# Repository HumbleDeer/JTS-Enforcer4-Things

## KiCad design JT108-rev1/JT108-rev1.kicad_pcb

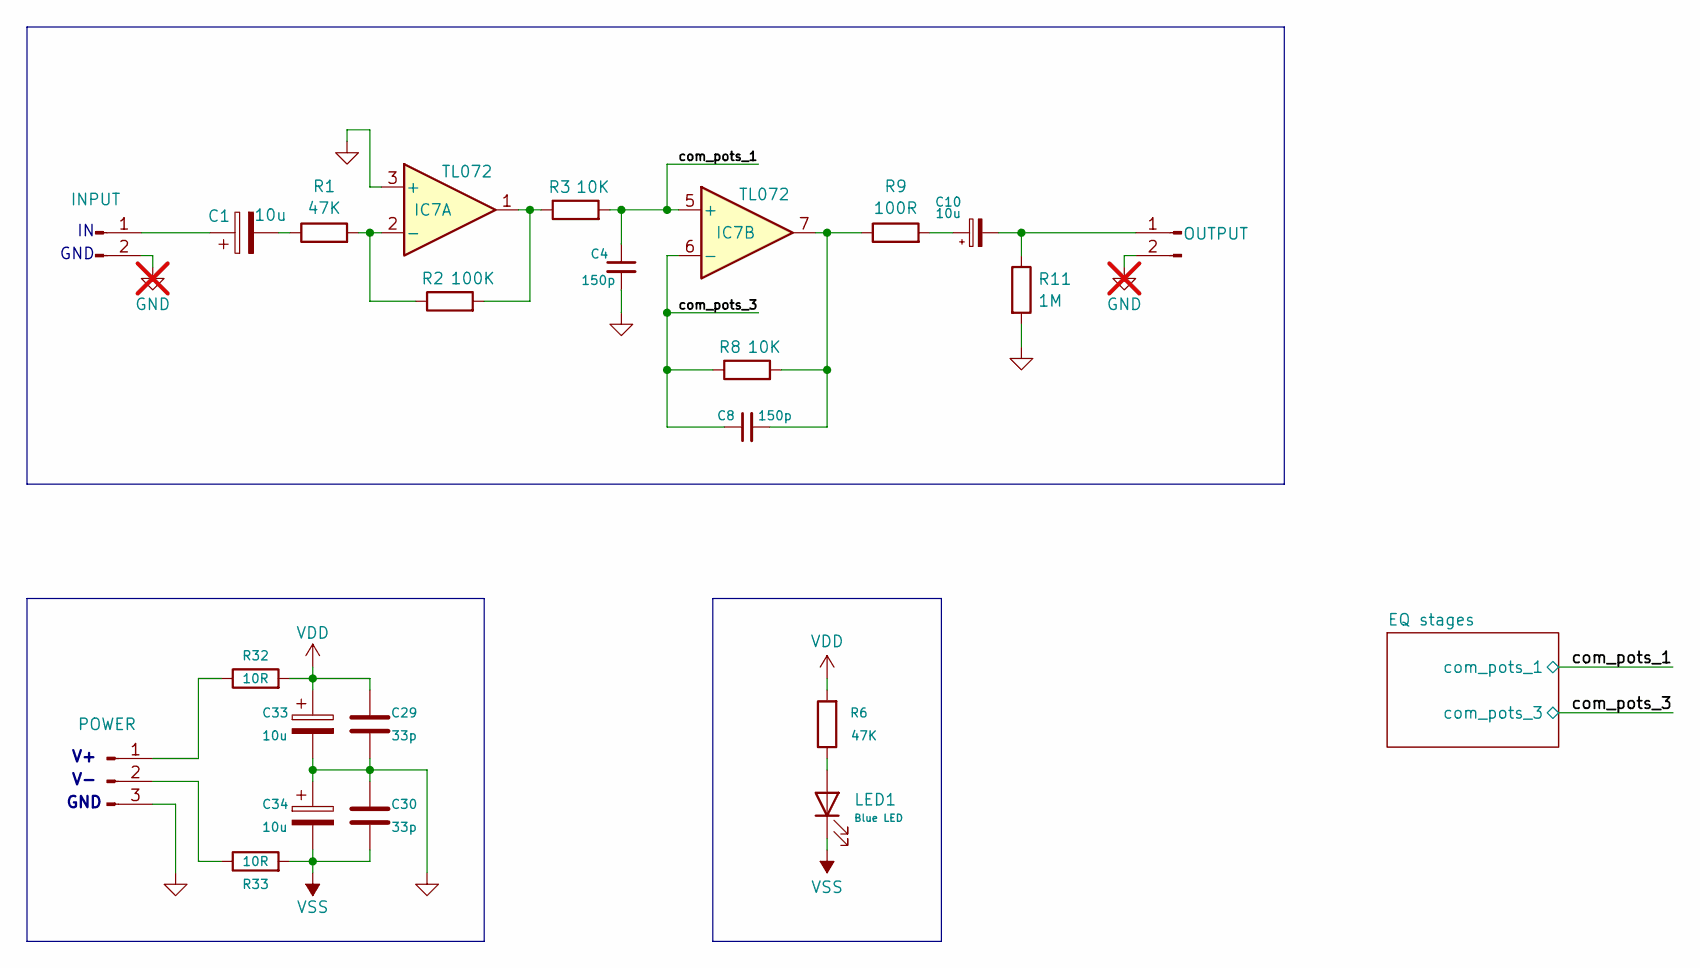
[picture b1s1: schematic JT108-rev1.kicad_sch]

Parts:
C1: 10u; CP_Radial_D5.0mm_P2.00mm
C4, C8: 150p; C_Disc_D5.0mm_W2.5mm_P2.50mm
C10, C33, C34: 10u; CP_Radial_D6.3mm_P2.50mm
C29, C30: 33p; C_Disc_D5.0mm_W2.5mm_P2.50mm
IC7: TL072; DIP-8_W7.62mm
J1: INPUT; PinHeader_1x01_P2.54mm_Vertical
J2: OUTPUT; PinHeader_1x01_P2.54mm_Vertical
J3: POWER; JST_VH_B3P-VH_1x03_P3.96mm_Vertical
LED1: Blue LED; LED_D5.0mm
R1: 47K; R_Axial_DIN0207_L6.3mm_D2.5mm_P10.16mm_Horizontal
R2: 100K; R_Axial_DIN0207_L6.3mm_D2.5mm_P10.16mm_Horizontal
R3, R8: 10K; R_Axial_DIN0207_L6.3mm_D2.5mm_P10.16mm_Horizontal
R6: 47K; R_Axial_DIN0207_L6.3mm_D2.5mm_P2.54mm_Vertical
R9: 100R; R_Axial_DIN0207_L6.3mm_D2.5mm_P10.16mm_Horizontal
R11: 1M; R_Axial_DIN0207_L6.3mm_D2.5mm_P10.16mm_Horizontal
R32, R33: 10R; R_Axial_DIN0207_L6.3mm_D2.5mm_P10.16mm_Horizontal

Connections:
/com_pots_1: C4.1, IC7.5 (+), R3.2; also elsewhere on the board
/com_pots_3: C8.1, IC7.6 (-), R8.1; also elsewhere on the board
GND: C4.2, C29.1, C30.1, C33.2, C34.1, IC7.3 (+), J1.2, J2.2, J3.3, R11.2; also elsewhere on the board
unnamed: C1.2, R1.1
unnamed: C8.2, IC7.7, R8.2, R9.1
unnamed: C10.1, R9.2
unnamed: IC7.1, R2.2, R3.1
unnamed: IC7.2 (-), R1.2, R2.1
unnamed: C1.1, J1.1 (Pin_1_1)
unnamed: C10.2, J2.1 (Pin_1_1), R11.1
unnamed: J3.1, R32.1
unnamed: J3.2, R33.1
unnamed: LED1.2 (A), R6.1
VDD: C29.2, C33.1, R6.2, R32.2; also elsewhere on the board
VSS: C30.2, C34.2, LED1.1 (K), R33.2; also elsewhere on the board

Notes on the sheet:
GND

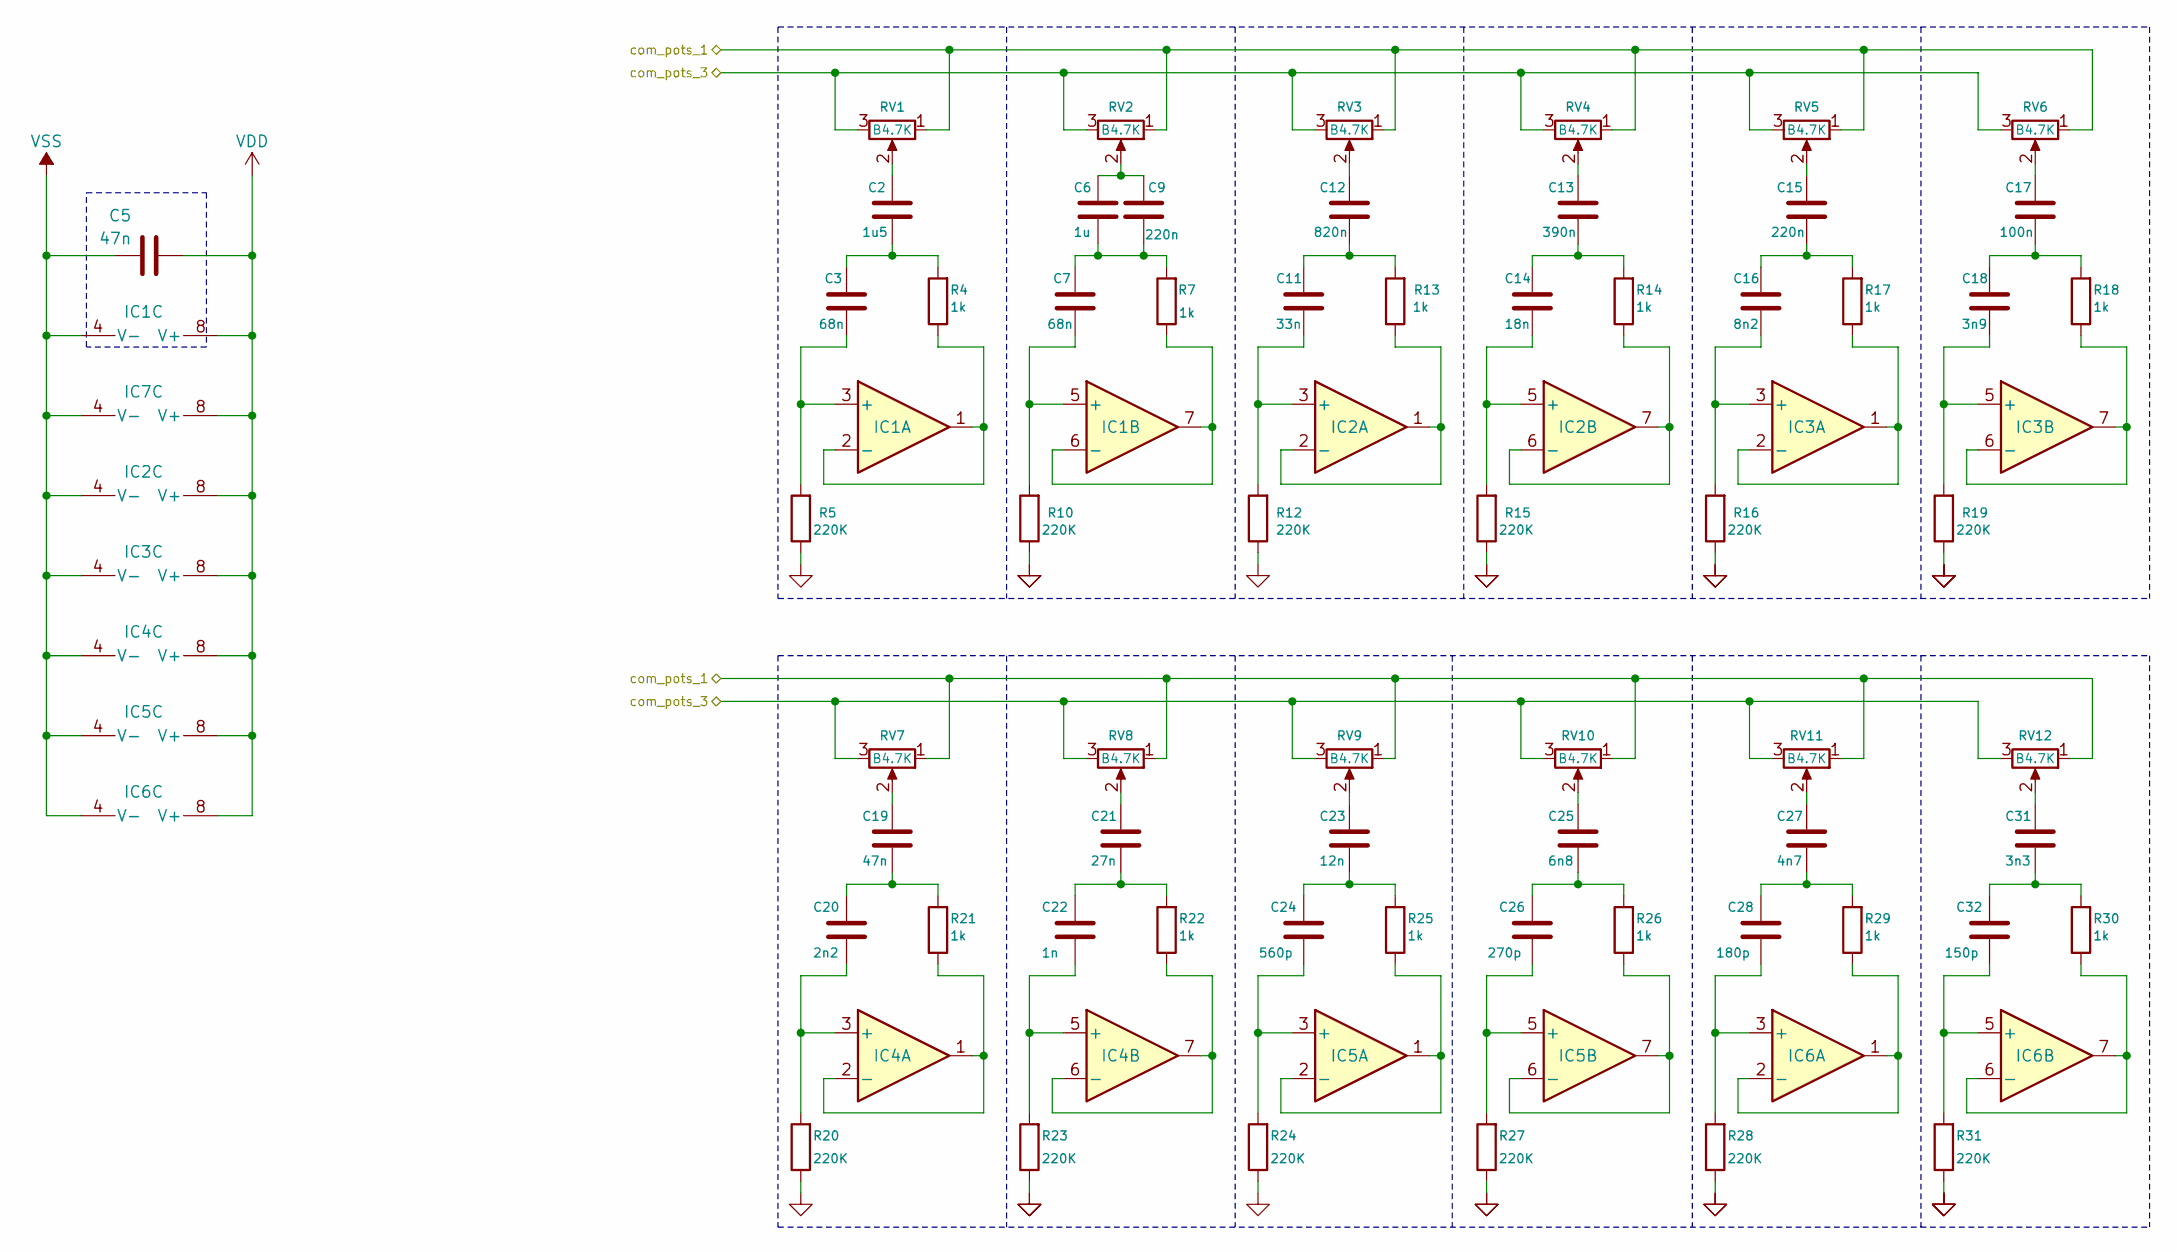
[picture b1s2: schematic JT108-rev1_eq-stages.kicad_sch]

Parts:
C2: 1u5; C_Rect_L7.2mm_W6.0mm_P5.00mm; Voltage/Tolerance k63
C3: 68n; C_Rect_L7.2mm_W3.5mm_P5.00mm_FKS2_FKP2_MKS2_MKP2
C5: 47n; C_Disc_D5.0mm_W2.5mm_P2.50mm
C6: 1u; C_Rect_L7.2mm_W5.5mm_P5.00mm_FKS2_FKP2_MKS2_MKP2; Voltage/Tolerance k63
C7: 68n; C_Rect_L7.2mm_W2.5mm_P5.00mm
C9, C15: 220n; C_Rect_L7.2mm_W3.5mm_P5.00mm_FKS2_FKP2_MKS2_MKP2; Voltage/Tolerance k63
C11: 33n; C_Rect_L7.2mm_W2.5mm_P5.00mm
C12: 820n; C_Rect_L7.2mm_W5.0mm_P5.00mm; Voltage/Tolerance k63
C13: 390n; C_Rect_L7.2mm_W5.0mm_P5.00mm; Voltage/Tolerance k63
C14: 18n; C_Rect_L7.2mm_W5.0mm_P5.00mm
C16: 8n2; C_Rect_L7.2mm_W7.2mm_P5.00mm
C17: 100n; C_Rect_L7.2mm_W2.5mm_P5.00mm; Voltage/Tolerance k63
C18: 3n9; C_Rect_L7.2mm_W3.5mm_P5.00mm_FKS2_FKP2_MKS2_MKP2
C19: 47n; C_Rect_L7.2mm_W2.5mm_P5.00mm; Voltage/Tolerance k63
C20: 2n2; C_Rect_L7.2mm_W2.5mm_P5.00mm
C21: 27n; C_Disc_D5.0mm_W2.5mm_P2.50mm; Voltage/Tolerance k63
C22: 1n; C_Rect_L7.2mm_W3.5mm_P5.00mm_FKS2_FKP2_MKS2_MKP2
C23: 12n; C_Rect_L7.2mm_W2.5mm_P5.00mm; Voltage/Tolerance k63
C24: 560p; C_Disc_D5.0mm_W2.5mm_P2.50mm
C25: 6n8; C_Rect_L7.2mm_W3.5mm_P5.00mm_FKS2_FKP2_MKS2_MKP2; Voltage/Tolerance k63
C26: 270p; C_Disc_D5.0mm_W2.5mm_P2.50mm
C27: 4n7; C_Rect_L7.2mm_W2.5mm_P5.00mm; Voltage/Tolerance k63
C28: 180p; C_Disc_D5.0mm_W2.5mm_P2.50mm
C31: 3n3; C_Rect_L7.2mm_W2.5mm_P5.00mm; Voltage/Tolerance k63
C32: 150p; C_Disc_D5.0mm_W2.5mm_P2.50mm
IC1, IC2, IC3, IC4, IC5, IC6, IC7: TL072; DIP-8_W7.62mm
R4, R7, R13, R14, R17, R18, R21, R22, R25, R26, R29, R30: 1k; R_Axial_DIN0207_L6.3mm_D2.5mm_P10.16mm_Horizontal
R5, R10, R12, R15, R16, R19, R20, R23, R24, R27, R28, R31: 220K; R_Axial_DIN0207_L6.3mm_D2.5mm_P10.16mm_Horizontal
RV1, RV2, RV3, RV4, RV5, RV6, RV7, RV8, RV9, RV10, RV11, RV12: B4.7K; Potentiometer_Alps_RK163_Single_Horizontal

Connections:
/com_pots_1: RV1.1, RV2.1, RV3.1, RV4.1, RV5.1, RV6.1, RV7.1, RV8.1, RV9.1, RV10.1, RV11.1, RV12.1; also elsewhere on the board
/com_pots_3: RV1.3, RV2.3, RV3.3, RV4.3, RV5.3, RV6.3, RV7.3, RV8.3, RV9.3, RV10.3, RV11.3, RV12.3; also elsewhere on the board
GND: R5.1, R10.1, R12.1, R15.1, R16.1, R19.1, R20.1, R23.1, R24.1, R27.1, R28.1, R31.1; also elsewhere on the board
unnamed: C2.1, RV1.2
unnamed: C2.2, C3.2, R4.2
unnamed: C6.1, C9.1, RV2.2
unnamed 7: C6.2, C7.2, C9.2, R7.2; also elsewhere on the board
unnamed: C11.2, C12.2, R13.2
unnamed: C12.1, RV3.2
unnamed: C13.1, RV4.2
unnamed: C13.2, C14.2, R14.2
unnamed: C15.1, RV5.2
unnamed: C15.2, C16.2, R17.2
unnamed: C17.1, RV6.2
unnamed: C17.2, C18.2, R18.2
unnamed: C19.1, RV7.2
unnamed: C19.2, C20.2, R21.2
unnamed: C21.1, RV8.2
unnamed: C21.2, C22.2, R22.2
unnamed: C23.1, RV9.2
unnamed: C23.2, C24.2, R25.2
unnamed: C25.1, RV10.2
unnamed: C25.2, C26.2, R26.2
unnamed: C27.1, RV11.2
unnamed: C27.2, C28.2, R29.2
unnamed: C31.1, RV12.2
unnamed: C31.2, C32.2, R30.2
unnamed: C3.1, IC1.3 (+), R5.2
unnamed: IC1.1, IC1.2 (-), R4.1
unnamed: C7.1, IC1.5 (+), R10.2
unnamed 33: IC1.6 (-), IC1.7, R7.1; also elsewhere on the board
unnamed: C11.1, IC2.3 (+), R12.2
unnamed: IC2.1, IC2.2 (-), R13.1
unnamed: C14.1, IC2.5 (+), R15.2
unnamed: IC2.6 (-), IC2.7, R14.1
unnamed: C16.1, IC3.3 (+), R16.2
unnamed: IC3.1, IC3.2 (-), R17.1
unnamed: C18.1, IC3.5 (+), R19.2
unnamed: IC3.6 (-), IC3.7, R18.1
unnamed: C20.1, IC4.3 (+), R20.2
unnamed: IC4.1, IC4.2 (-), R21.1
unnamed: C22.1, IC4.5 (+), R23.2
unnamed: IC4.6 (-), IC4.7, R22.1
unnamed: C24.1, IC5.3 (+), R24.2
unnamed: IC5.1, IC5.2 (-), R25.1
unnamed: C26.1, IC5.5 (+), R27.2
unnamed: IC5.6 (-), IC5.7, R26.1
unnamed: C28.1, IC6.3 (+), R28.2
unnamed: IC6.1, IC6.2 (-), R29.1
unnamed: C32.1, IC6.5 (+), R31.2
unnamed: IC6.6 (-), IC6.7, R30.1
VDD: C5.1, IC1.8 (V+), IC2.8 (V+), IC3.8 (V+), IC4.8 (V+), IC5.8 (V+), IC6.8 (V+), IC7.8 (V+); also elsewhere on the board
VSS: C5.2, IC1.4 (V-), IC2.4 (V-), IC3.4 (V-), IC4.4 (V-), IC5.4 (V-), IC6.4 (V-), IC7.4 (V-); also elsewhere on the board

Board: 2 copper layers, 93 parts (0 on the bottom side), 63 nets, no tracks yet.

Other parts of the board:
C35: 33p; C_Disc_D5.0mm_W2.5mm_P2.50mm
D1: Blue LED; LED_D5.0mm
R7#2: 1k; R_Axial_DIN0207_L6.3mm_D2.5mm_P10.16mm_Horizontal

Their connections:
GND: C35.1; also elsewhere on the board
unnamed 7: R7#2.2; also elsewhere on the board
unnamed 33: R7#2.1; also elsewhere on the board
VDD: C35.2; also elsewhere on the board

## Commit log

2026-05-06 Added all meta & physical values for components relating to one section and the PSU in stage // ready to trace PCB out & reconstruct schematic from that.
2026-05-08 Finished schematic & drawings. PCB unfinished.
